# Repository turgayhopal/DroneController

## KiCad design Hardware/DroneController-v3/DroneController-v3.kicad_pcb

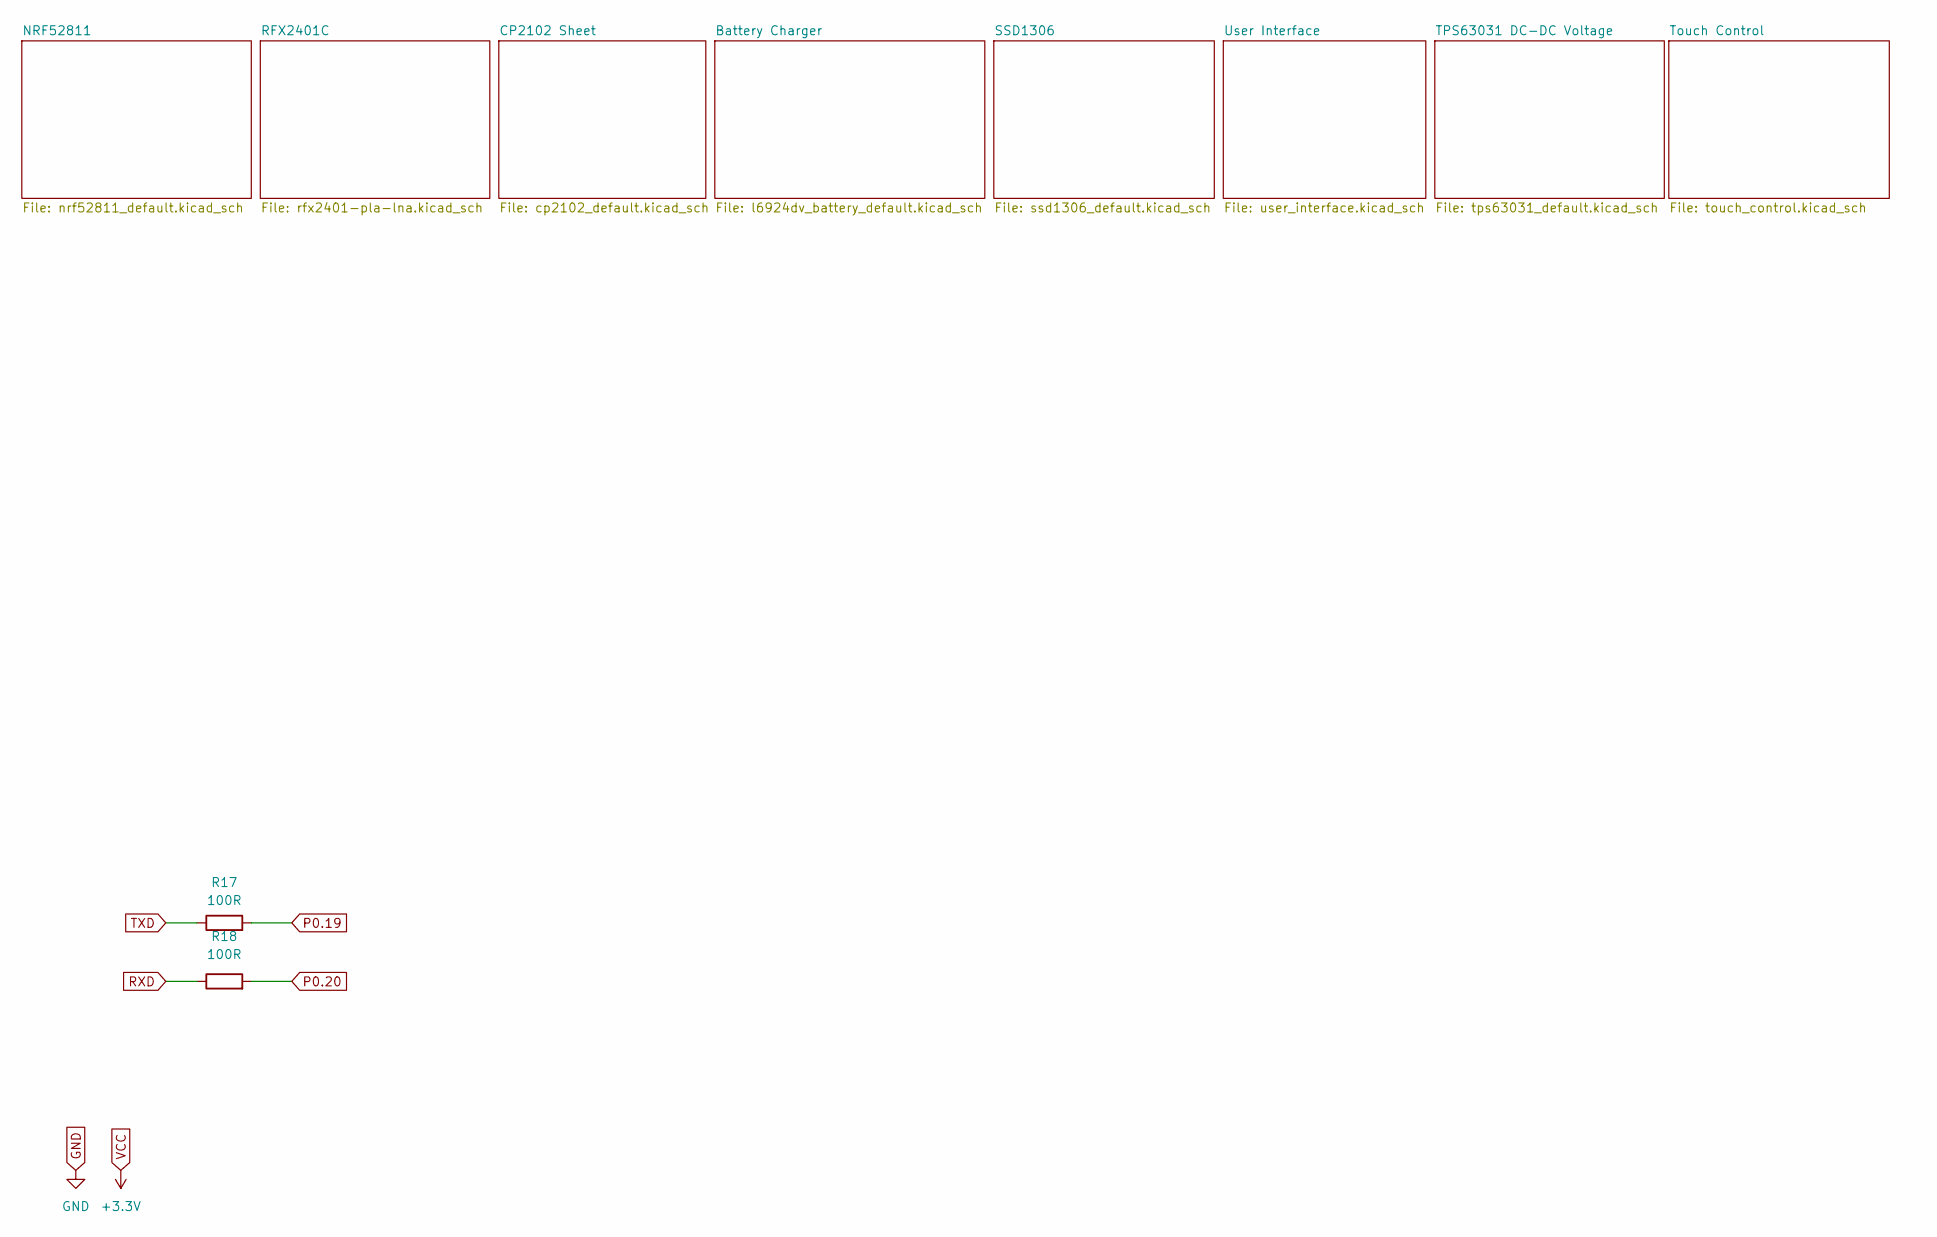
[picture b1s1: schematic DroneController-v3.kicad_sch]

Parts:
R17, R18: 100R; R_0603_1608Metric

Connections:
P0.19: R17.2; also elsewhere on the board
P0.20: R18.2; also elsewhere on the board
RXD: R18.1; also elsewhere on the board
TXD: R17.1; also elsewhere on the board

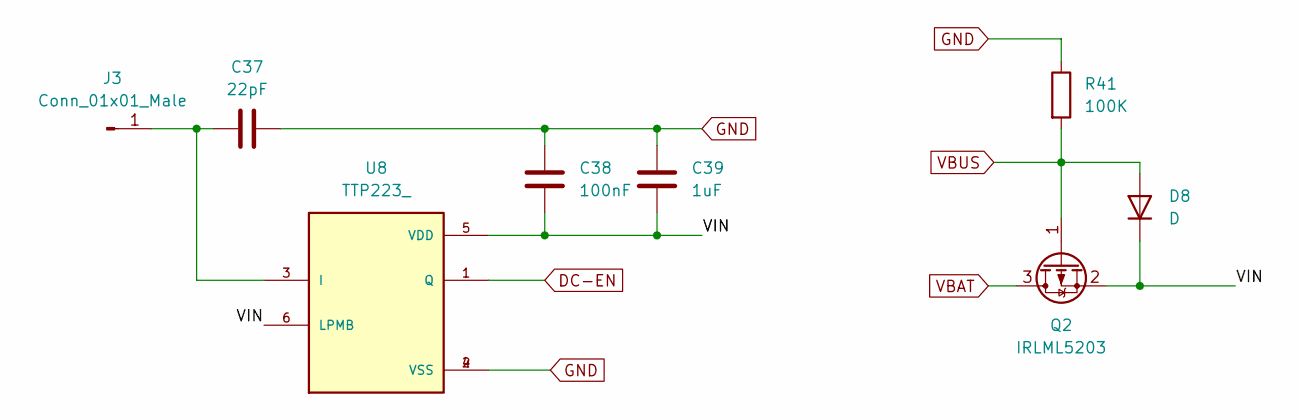
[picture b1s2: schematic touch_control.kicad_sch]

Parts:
C37: 22pF; C_0603_1608Metric
C38: 100nF; C_0603_1608Metric
C39: 1uF; C_0603_1608Metric
D8: D; D_0805_2012Metric
J3: Conn_01x01_Male; TestPoint_Pad_D4.0mm
Q2: IRLML5203; SOT-23
R41: 100K; R_0603_1608Metric
U8: TTP223_; SOT95P285X126-6N; PARTREV 2.0

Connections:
/Touch Control/VIN: C38.1, C39.1, D8.1 (K), Q2.2 (S), U8.5 (VDD), U8.6 (LPMB)
DC-EN: U8.1 (Q); also elsewhere on the board
GND: C37.2, C38.2, C39.2, R41.1, U8.2 (VSS), U8.4 (VSS); also elsewhere on the board
unnamed: C37.1, J3.1, U8.3 (I)
VBAT: Q2.3 (D); also elsewhere on the board
VBUS: D8.2 (A), Q2.1 (G), R41.2; also elsewhere on the board

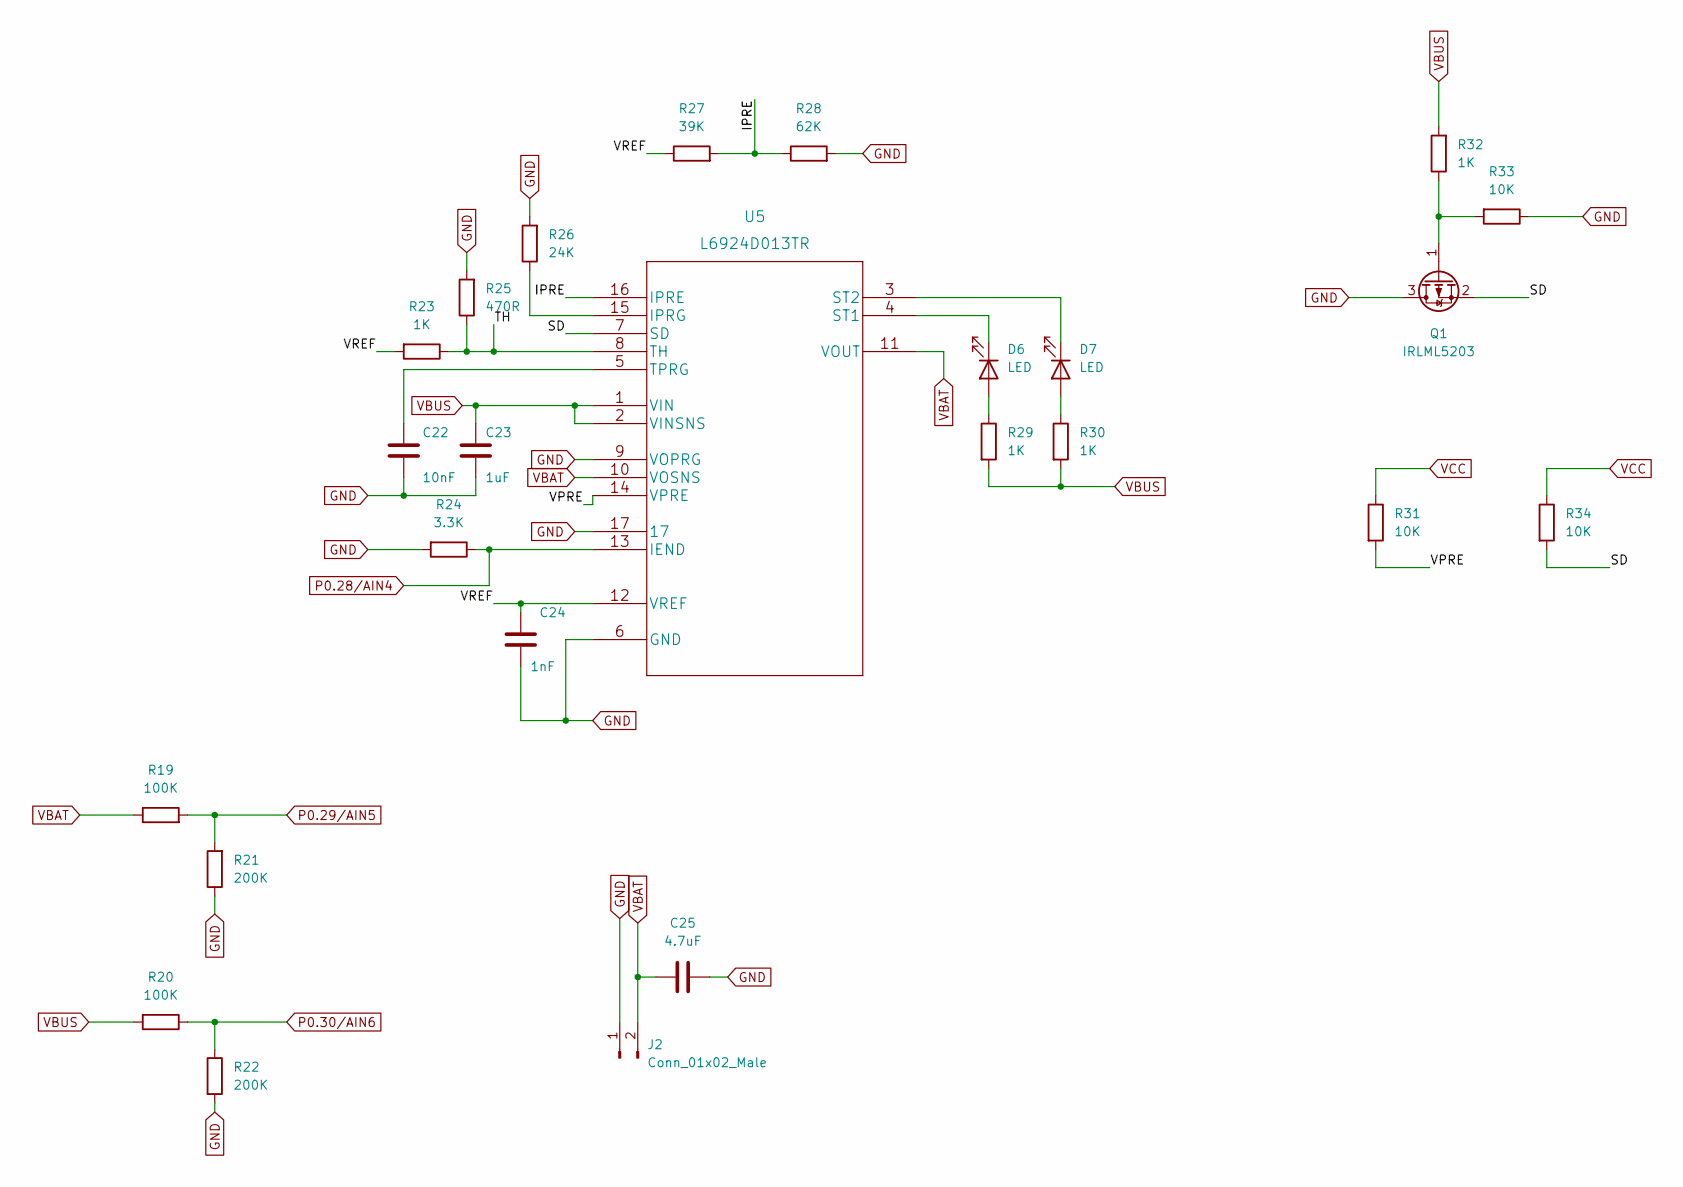
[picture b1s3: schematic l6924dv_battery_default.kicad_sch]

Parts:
C22: 10nF; C_0603_1608Metric
C23: 1uF; C_0603_1608Metric
C24: 1nF; C_0603_1608Metric
C25: 4.7uF; C_0603_1608Metric
D6, D7: LED; LED_0805_2012Metric
J2: Conn_01x02_Male; PinHeader_1x02_P2.54mm_Vertical
Q1: IRLML5203; SOT-23
R19, R20: 100K; R_0603_1608Metric
R21, R22: 200K; R_0603_1608Metric
R23, R29, R30, R32: 1K; R_0603_1608Metric
R24: 3.3K; R_0603_1608Metric
R25: 470R; R_0603_1608Metric
R26: 24K; R_0603_1608Metric
R27: 39K; R_0603_1608Metric
R28: 62K; R_0603_1608Metric
R31, R33, R34: 10K; R_0603_1608Metric
U5: L6924D013TR

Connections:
/Battery Charger/IPRE: R27.2, R28.1, U5.16 (IPRE)
/Battery Charger/SD: Q1.2 (S), R34.2, U5.7 (SD)
/Battery Charger/TH: R23.1, R25.1, U5.8 (TH)
/Battery Charger/VPRE: R31.2, U5.14 (VPRE)
/Battery Charger/VREF: C24.1, R23.2, R27.1, U5.12 (VREF)
GND: C22.2, C23.2, C24.2, C25.2, J2.1, Q1.3 (D), R21.1, R22.2, R24.2, R25.2, R26.2, R28.2, R33.1, U5.6 (GND), U5.9 (VOPRG), U5.17; also elsewhere on the board
unnamed: C22.1, U5.5 (TPRG)
unnamed: D6.1 (K), U5.4 (ST1)
unnamed: D6.2 (A), R29.1
unnamed: D7.1 (K), U5.3 (ST2)
unnamed: D7.2 (A), R30.1
unnamed: Q1.1 (G), R32.1, R33.2
unnamed: R26.1, U5.15 (IPRG)
P0.28/AIN4: R24.1, U5.13 (IEND); also elsewhere on the board
P0.29/AIN5: R19.2, R21.2; also elsewhere on the board
P0.30/AIN6: R20.1, R22.1; also elsewhere on the board
VBAT: C25.1, J2.2, R19.1, U5.10 (VOSNS), U5.11 (VOUT); also elsewhere on the board
VBUS: C23.1, R20.2, R29.2, R30.2, R32.2, U5.1 (VIN), U5.2 (VINSNS); also elsewhere on the board
VCC: R31.1, R34.1; also elsewhere on the board

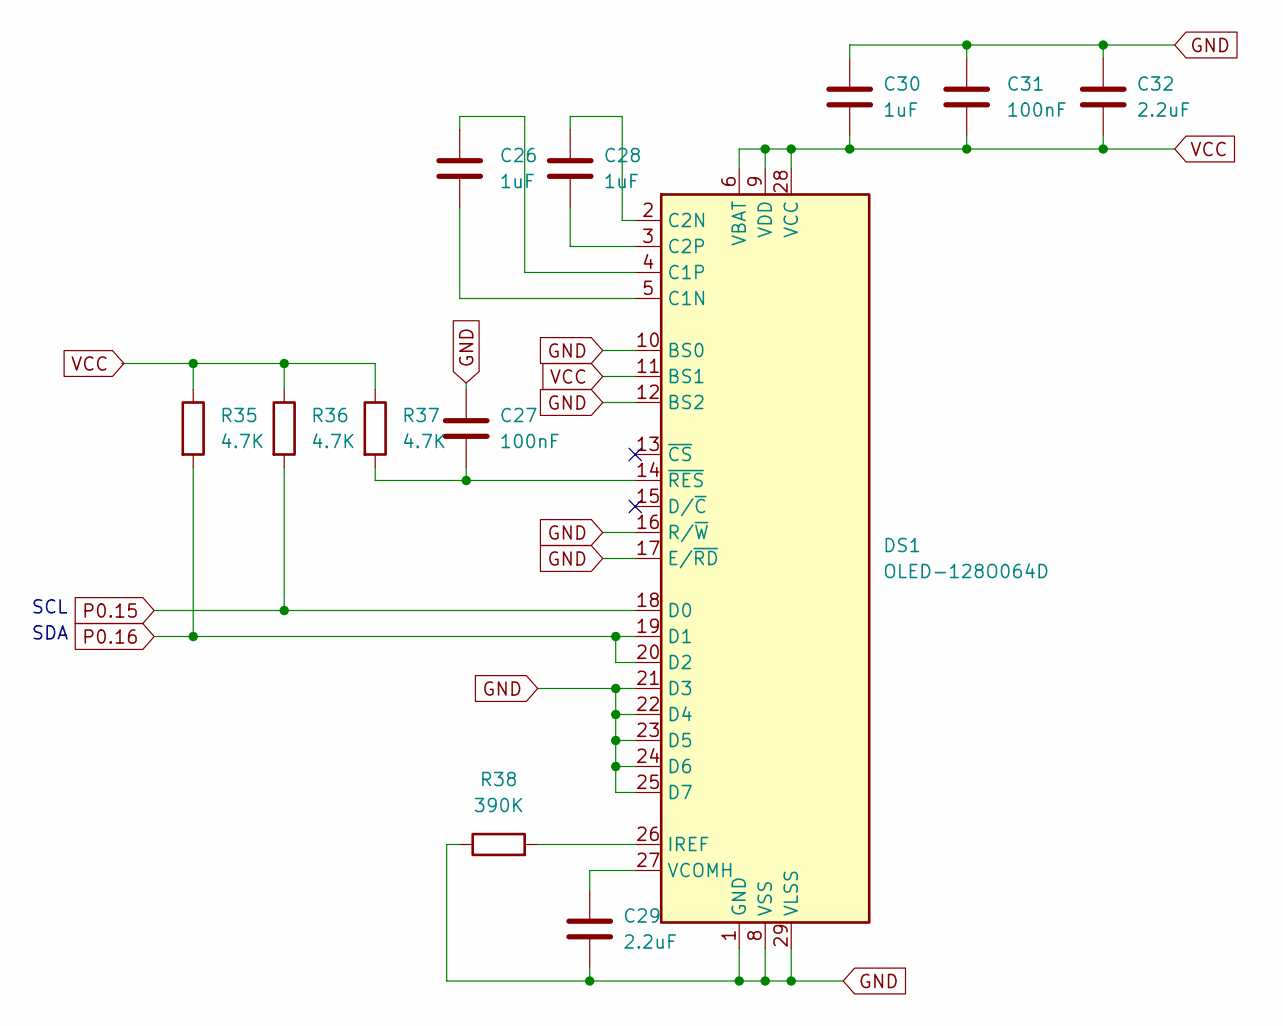
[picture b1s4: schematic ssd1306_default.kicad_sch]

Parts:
C26, C28, C30: 1uF; C_0603_1608Metric
C27, C31: 100nF; C_0603_1608Metric
C29, C32: 2.2uF; C_0603_1608Metric
DS1: OLED-128O064D
R35, R36, R37: 4.7K; R_0603_1608Metric
R38: 390K; R_0603_1608Metric

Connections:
GND: C27.2, C29.1, C30.2, C31.2, C32.2, DS1.1 (GND), DS1.8 (VSS), DS1.10 (BS0), DS1.12 (BS2), DS1.16 (R/~W), DS1.17 (E/~RD), DS1.21 (D3), DS1.22 (D4), DS1.23 (D5), DS1.24 (D6), DS1.25 (D7), DS1.29 (VLSS), DS1.30 (GND), R38.1; also elsewhere on the board
unnamed: C26.1, DS1.5 (C1N)
unnamed: C26.2, DS1.4 (C1P)
unnamed: C27.1, DS1.14 (~RES), R37.2
unnamed: C28.1, DS1.3 (C2P)
unnamed: C28.2, DS1.2 (C2N)
unnamed: C29.2, DS1.27 (VCOMH)
unnamed: DS1.26 (IREF), R38.2
P0.15: DS1.18 (D0), R36.2; also elsewhere on the board
P0.16: DS1.19 (D1), DS1.20 (D2), R35.2; also elsewhere on the board
VCC: C30.1, C31.1, C32.1, DS1.6 (VBAT), DS1.9 (VDD), DS1.11 (BS1), DS1.28 (VCC), R35.1, R36.1, R37.1; also elsewhere on the board

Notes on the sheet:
SCL
SDA

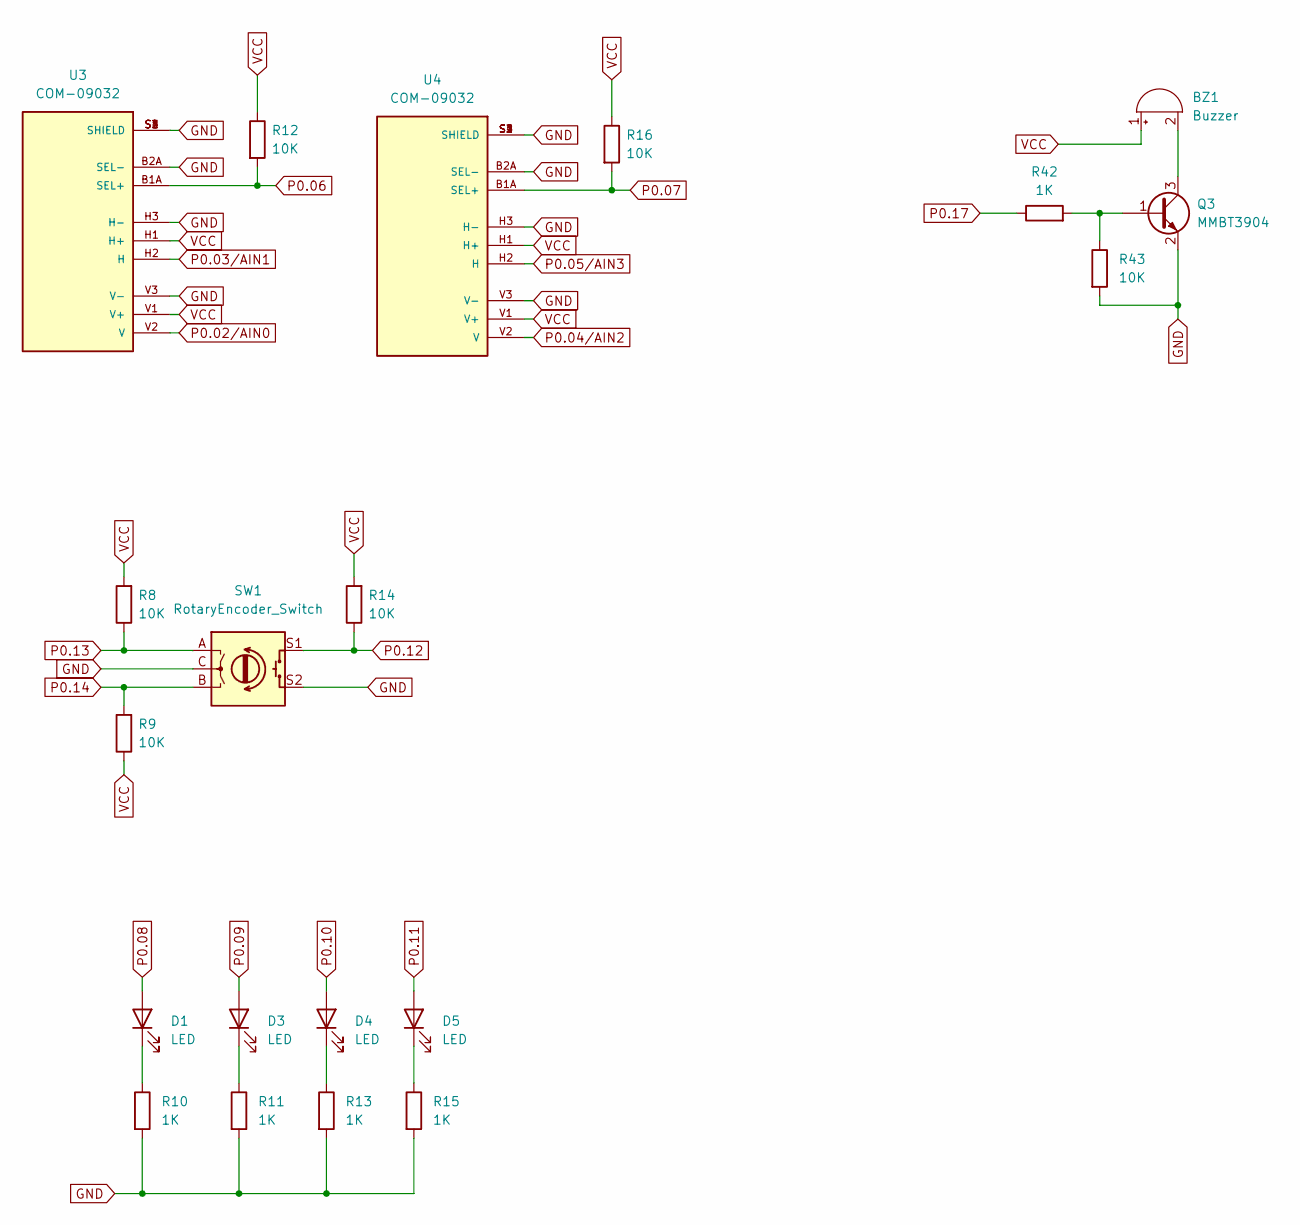
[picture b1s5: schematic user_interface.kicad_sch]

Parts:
BZ1: Buzzer; Buzzer_12x9.5RM7.6
D1, D3, D4, D5: LED; LED_0805_2012Metric
Q3: MMBT3904; SOT-23
R8, R9, R12, R14, R16, R43: 10K; R_0603_1608Metric
R10, R11, R13, R15, R42: 1K; R_0603_1608Metric
SW1: RotaryEncoder_Switch; RotaryEncoder_Alps_EC12E-Switch_Vertical_H20mm
U3, U4: COM-09032; XDCR_COM-09032; PARTREV N/A

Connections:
GND: Q3.2 (E), R10.2, R11.2, R13.2, R15.2, R43.2, SW1.C, SW1.S2, U3.B2A (SEL-), U3.H3 (H-), U3.S1 (SHIELD), U3.S2 (SHIELD), U3.S3 (SHIELD), U3.S4 (SHIELD), U3.V3 (V-), U4.B2A (SEL-), U4.H3 (H-), U4.S1 (SHIELD), U4.S2 (SHIELD), U4.S3 (SHIELD), U4.S4 (SHIELD), U4.V3 (V-); also elsewhere on the board
unnamed: BZ1.2 (+), Q3.3 (C)
unnamed: D1.1 (K), R10.1
unnamed: D3.1 (K), R11.1
unnamed: D4.1 (K), R13.1
unnamed: D5.1 (K), R15.1
unnamed: Q3.1 (B), R42.2, R43.1
P0.02/AIN0: U3.V2 (V); also elsewhere on the board
P0.03/AIN1: U3.H2 (H); also elsewhere on the board
P0.04/AIN2: U4.V2 (V); also elsewhere on the board
P0.05/AIN3: U4.H2 (H); also elsewhere on the board
P0.06: R12.2, U3.B1A (SEL+); also elsewhere on the board
P0.07: R16.2, U4.B1A (SEL+); also elsewhere on the board
P0.08: D1.2 (A); also elsewhere on the board
P0.09: D3.2 (A); also elsewhere on the board
P0.10: D4.2 (A); also elsewhere on the board
P0.11: D5.2 (A); also elsewhere on the board
P0.12: R14.1, SW1.S1; also elsewhere on the board
P0.13: R8.1, SW1.A; also elsewhere on the board
P0.14: R9.2, SW1.B; also elsewhere on the board
P0.17: R42.1; also elsewhere on the board
VCC: BZ1.1 (-), R8.2, R9.1, R12.1, R14.2, R16.1, U3.H1 (H+), U3.V1 (V+), U4.H1 (H+), U4.V1 (V+); also elsewhere on the board

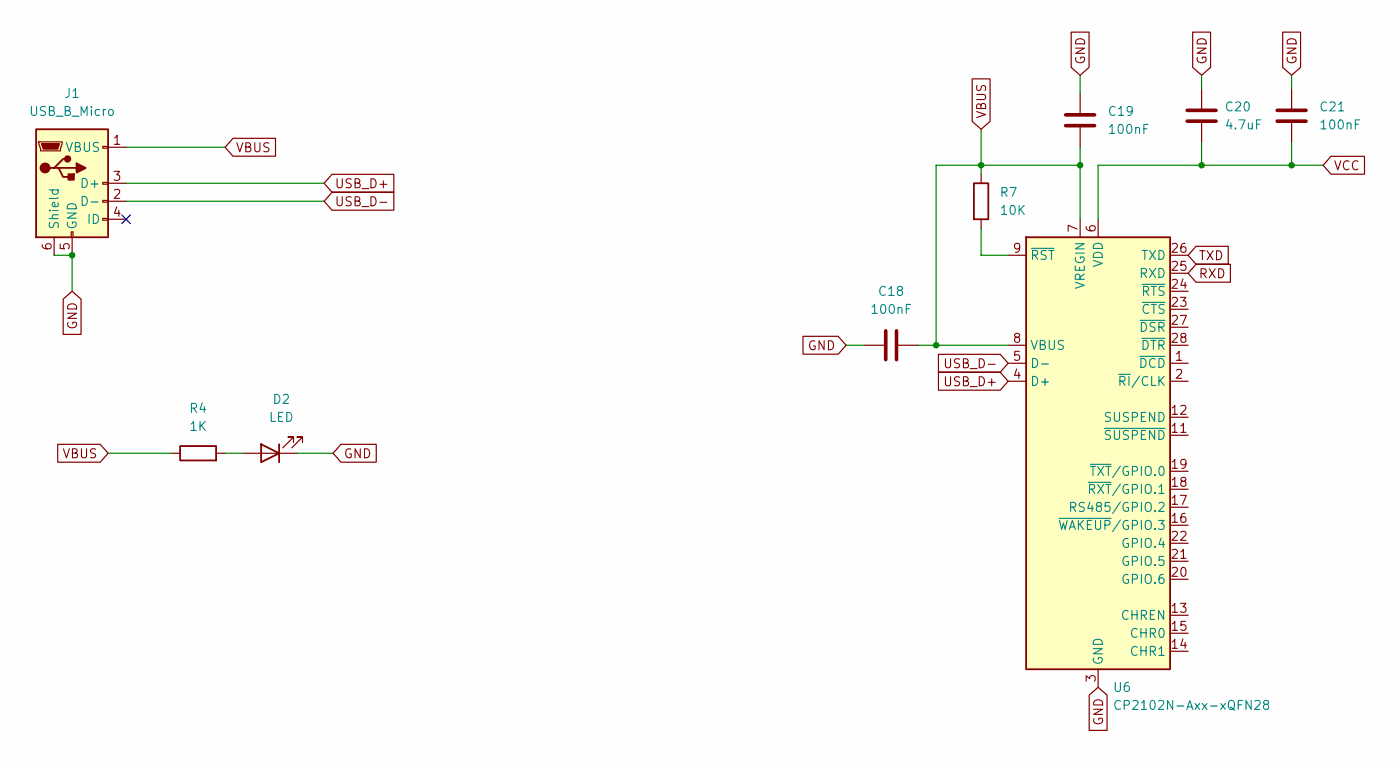
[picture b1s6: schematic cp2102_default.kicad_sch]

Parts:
C18, C19, C21: 100nF; C_0603_1608Metric
C20: 4.7uF; C_0603_1608Metric
D2: LED; LED_0603_1608Metric
J1: USB_B_Micro; USB_Micro-B_GCT_USB3076-30-A
R4: 1K; R_0603_1608Metric
R7: 10K; R_0603_1608Metric
U6: CP2102N-Axx-xQFN28; QFN-28-1EP_5x5mm_P0.5mm_EP3.35x3.35mm

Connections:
GND: C18.1, C19.2, C20.2, C21.2, D2.1 (K), J1.5 (GND), J1.6 (Shield), U6.3 (GND), U6.29 (GND); also elsewhere on the board
unnamed: D2.2 (A), R4.2
unnamed: R7.2, U6.9 (~RST)
RXD: U6.25 (RXD); also elsewhere on the board
TXD: U6.26 (TXD); also elsewhere on the board
USB_D+: J1.3 (D+), U6.4 (D+)
USB_D-: J1.2 (D-), U6.5 (D-)
VBUS: C18.2, C19.1, J1.1 (VBUS), R4.1, R7.1, U6.7 (VREGIN), U6.8 (VBUS); also elsewhere on the board
VCC: C20.1, C21.1, U6.6 (VDD); also elsewhere on the board

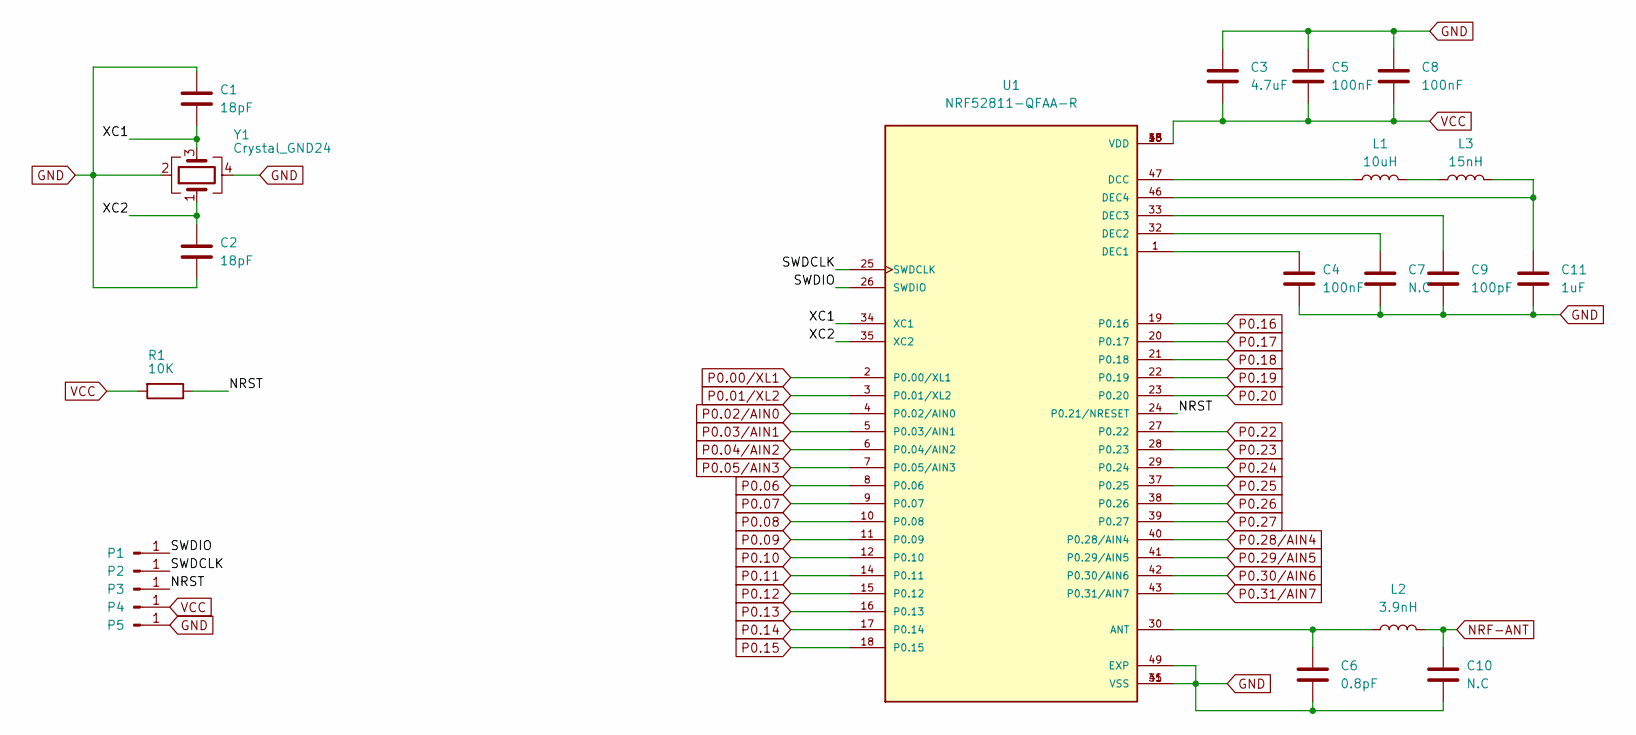
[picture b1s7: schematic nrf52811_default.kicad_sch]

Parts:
C1, C2: 18pF; C_0603_1608Metric
C3: 4.7uF; C_0603_1608Metric
C4, C5, C8: 100nF; C_0603_1608Metric
C6: 0.8pF; C_0603_1608Metric
C7, C10: N.C; C_0603_1608Metric
C9: 100pF; C_0603_1608Metric
C11: 1uF; C_0603_1608Metric
L1: 10uH; L_0805_2012Metric
L2: 3.9nH; L_0805_2012Metric
L3: 15nH; L_0805_2012Metric
P1, P2, P3, P4, P5: Conn_01x01_Male; TestPoint_Pad_D2.0mm
R1: 10K; R_0603_1608Metric
U1: NRF52811-QFAA-R; QFN40P600X600X90-49N; PARTREV 1.0
Y1: Crystal_GND24; Crystal_SMD_3225-4Pin_3.2x2.5mm

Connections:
/NRF52811/NRST: P3.1, R1.1, U1.24 (P0.21/NRESET)
/NRF52811/SWDCLK: P2.1, U1.25 (SWDCLK)
/NRF52811/SWDIO: P1.1, U1.26 (SWDIO)
/NRF52811/XC1: C1.1, U1.34 (XC1), Y1.3
/NRF52811/XC2: C2.2, U1.35 (XC2), Y1.1
GND: C1.2, C2.1, C3.1, C4.2, C5.1, C6.2, C7.2, C8.1, C9.2, C10.2, C11.2, P5.1, U1.31 (VSS), U1.45 (VSS), U1.49 (EXP), Y1.2, Y1.4; also elsewhere on the board
NRF-ANT: C10.1, L2.2; also elsewhere on the board
unnamed: C4.1, U1.1 (DEC1)
unnamed: C6.1, L2.1, U1.30 (ANT)
unnamed: C7.1, U1.32 (DEC2)
unnamed: C9.1, U1.33 (DEC3)
unnamed: C11.1, L3.2, U1.46 (DEC4)
unnamed: L1.1, U1.47 (DCC)
unnamed: L1.2, L3.1
P0.00/XL1: U1.2 (P0.00/XL1)
P0.01/XL2: U1.3 (P0.01/XL2)
P0.02/AIN0: U1.4 (P0.02/AIN0); also elsewhere on the board
P0.03/AIN1: U1.5 (P0.03/AIN1); also elsewhere on the board
P0.04/AIN2: U1.6 (P0.04/AIN2); also elsewhere on the board
P0.05/AIN3: U1.7 (P0.05/AIN3); also elsewhere on the board
P0.06: U1.8 (P0.06); also elsewhere on the board
P0.07: U1.9 (P0.07); also elsewhere on the board
P0.08: U1.10 (P0.08); also elsewhere on the board
P0.09: U1.11 (P0.09); also elsewhere on the board
P0.10: U1.12 (P0.10); also elsewhere on the board
P0.11: U1.14 (P0.11); also elsewhere on the board
P0.12: U1.15 (P0.12); also elsewhere on the board
P0.13: U1.16 (P0.13); also elsewhere on the board
P0.14: U1.17 (P0.14); also elsewhere on the board
P0.15: U1.18 (P0.15); also elsewhere on the board
P0.16: U1.19 (P0.16); also elsewhere on the board
P0.17: U1.20 (P0.17); also elsewhere on the board
P0.18: U1.21 (P0.18)
P0.19: U1.22 (P0.19); also elsewhere on the board
P0.20: U1.23 (P0.20); also elsewhere on the board
P0.22: U1.27 (P0.22)
P0.23: U1.28 (P0.23); also elsewhere on the board
P0.24: U1.29 (P0.24); also elsewhere on the board
P0.25: U1.37 (P0.25)
P0.26: U1.38 (P0.26)
P0.27: U1.39 (P0.27)
P0.28/AIN4: U1.40 (P0.28/AIN4); also elsewhere on the board
P0.29/AIN5: U1.41 (P0.29/AIN5); also elsewhere on the board
P0.30/AIN6: U1.42 (P0.30/AIN6); also elsewhere on the board
P0.31/AIN7: U1.43 (P0.31/AIN7)
VCC: C3.2, C5.2, C8.2, P4.1, R1.2, U1.13 (VDD), U1.36 (VDD), U1.48 (VDD); also elsewhere on the board

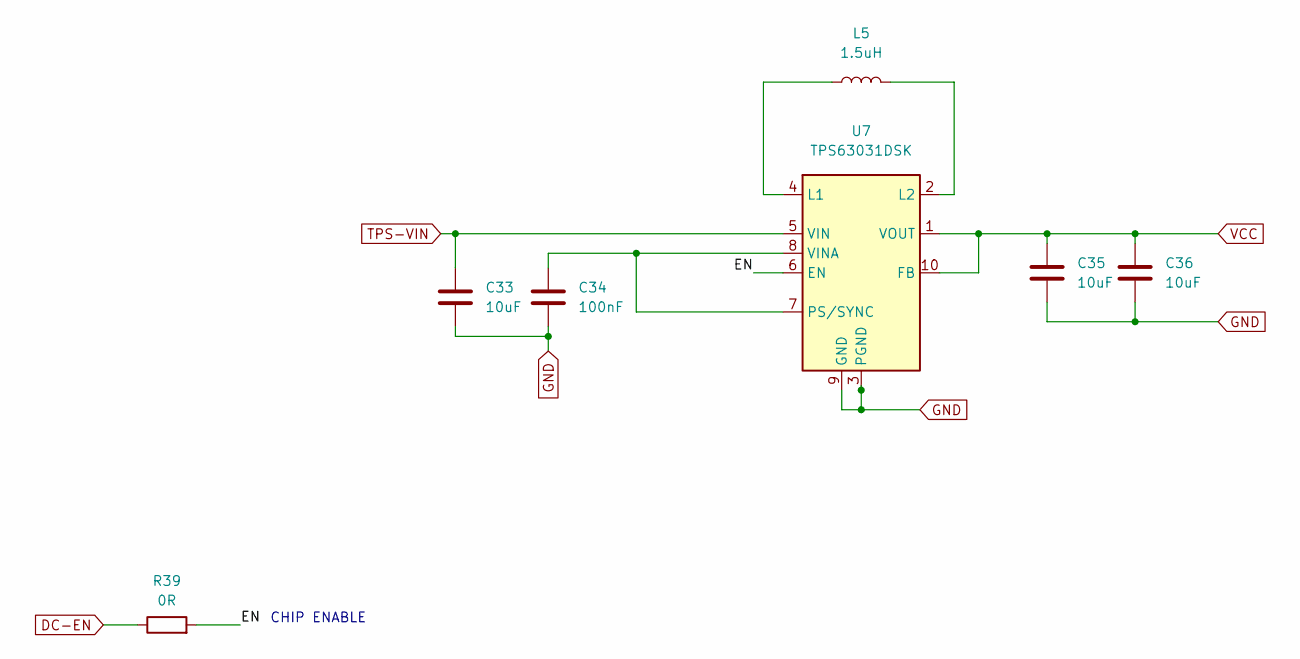
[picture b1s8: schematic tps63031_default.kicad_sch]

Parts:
C33, C35, C36: 10uF; C_0603_1608Metric
C34: 100nF; C_0603_1608Metric
L5: 1.5uH; L_Coilcraft_XxL4020
R39: 0R; R_0603_1608Metric
U7: TPS63031DSK; WSON-10-1EP_2.5x2.5mm_P0.5mm_EP1.2x2mm

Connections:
/TPS63031 DC-DC Voltage/EN: R39.2, U7.6 (EN)
DC-EN: R39.1; also elsewhere on the board
GND: C33.2, C34.2, C35.2, C36.2, U7.3 (PGND), U7.9 (GND), U7.11 (PGND); also elsewhere on the board
unnamed: C34.1, U7.7 (PS/SYNC), U7.8 (VINA)
unnamed: L5.1, U7.4 (L1)
unnamed: L5.2, U7.2 (L2)
TPS-VIN: C33.1, U7.5 (VIN)
VCC: C35.1, C36.1, U7.1 (VOUT), U7.10 (FB); also elsewhere on the board

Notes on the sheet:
CHIP ENABLE

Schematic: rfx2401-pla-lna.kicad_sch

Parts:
AE1: Antenna_Shield; SMA_Amphenol_132289_EdgeMount
C12: 0.3pF; C_0603_1608Metric
C13: 2.2uF; C_0603_1608Metric
C14, C16: 1.5pF; C_0603_1608Metric
C15: 10nF; C_0603_1608Metric
C17: 200pF; C_0603_1608Metric
L4: 2.4nH; L_0805_2012Metric
R2, R3: 10K; R_0603_1608Metric
U2: RFX2401C; QFN50P300X300X60-17N

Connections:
/RFX2401C/ANT: AE1.1 (A), C16.1, L4.2
GND: AE1.2 (Shield), C12.2, C13.1, C14.2, C15.1, C16.2, C17.1, U2.2 (GND), U2.3 (GND), U2.8 (GND), U2.9 (GND), U2.11 (GND), U2.17 (GND); also elsewhere on the board
NRF-ANT: U2.4 (TXRX); also elsewhere on the board
unnamed: C12.1, C14.1, L4.1, U2.10 (ANT)
unnamed: R2.2, U2.6 (RXEN)
unnamed: R3.2, U2.5 (TXEN)
P0.23: R2.1; also elsewhere on the board
P0.24: R3.1; also elsewhere on the board
VCC: C13.2, C15.2, C17.2, U2.14 (VDD), U2.16 (VDD); also elsewhere on the board

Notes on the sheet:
TXEN
RXEN

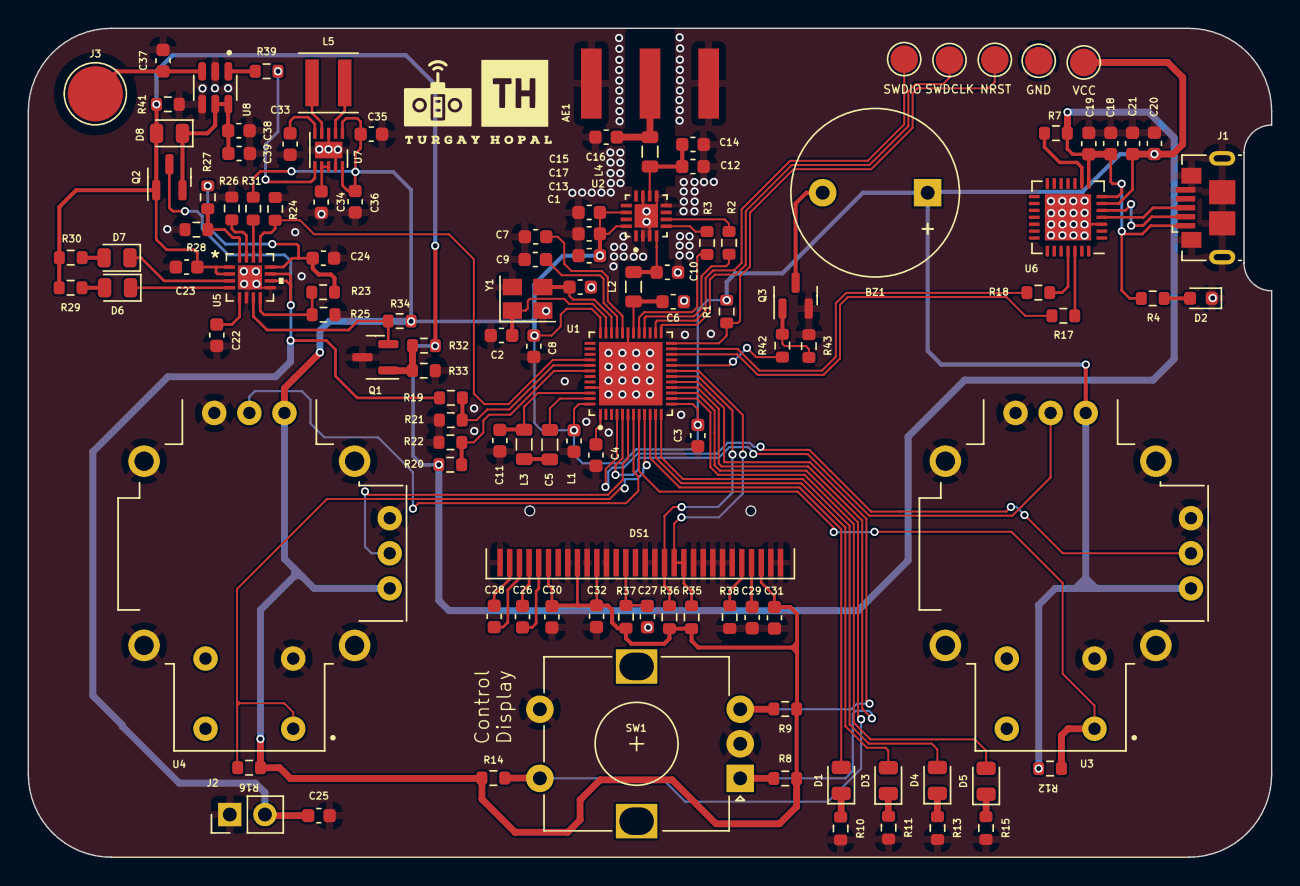
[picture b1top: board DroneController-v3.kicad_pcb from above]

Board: 2 copper layers, 90.0 x 60.0 mm, 116 parts (0 on the bottom side), 83 nets.

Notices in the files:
parts and their libraries:
Copyright 2021 Accelerated Designs. All rights reserved.
